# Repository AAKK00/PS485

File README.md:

# PS485
posision sensorとrs485とattinyを用いた角度取得モジュール

Arduinoスケッチ、DynamixelSlaveライブラリ、配線・書き込み手順は [arduino/README.md](arduino/README.md) を参照。

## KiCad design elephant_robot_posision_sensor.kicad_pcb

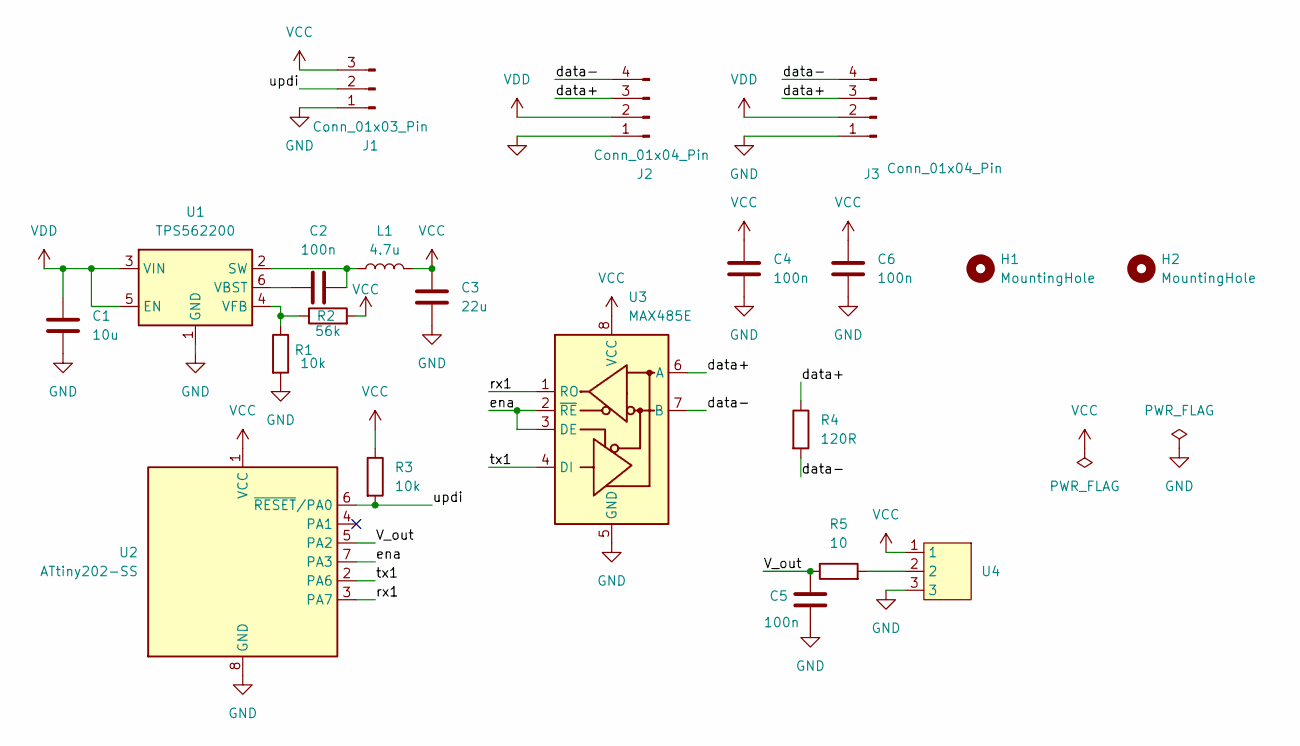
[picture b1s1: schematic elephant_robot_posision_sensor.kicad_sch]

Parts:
C1: 10u; C_0603_1608Metric
C2, C4, C5, C6: 100n; C_0603_1608Metric
C3: 22u; C_0603_1608Metric
H1, H2: MountingHole; MountingHole_2.2mm_M2
J1: Conn_01x03_Pin; PinHeader_1x03_P1.00mm_Vertical
J2, J3: Conn_01x04_Pin; JST_SH_SM04B-SRSS-TB_1x04-1MP_P1.00mm_Horizontal
L1: 4.7u; L_Cenker_CKCS201610
R1: 10k; R_0603_1608Metric
R2: 56k; R_0603_1608Metric
R3: 10k; C_0603_1608Metric
R4: 120R; C_0603_1608Metric
R5: 10; C_0603_1608Metric
U1: TPS562200; SOT-23-6
U2: ATtiny202-SS; SOIC-8_3.9x4.9mm_P1.27mm
U3: MAX485E; SOIC-8_3.9x4.9mm_P1.27mm
U4: RDC506018A

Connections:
/V_out: C5.1, R5.1, U2.5 (PA2)
/data+: J2.3, J3.3, R4.1, U3.6 (A)
/data-: J2.4, J3.4, R4.2, U3.7 (B)
/ena: U2.7 (PA3), U3.2 (~RE), U3.3 (DE)
/rx1: U2.3 (PA7), U3.1 (RO)
/tx1: U2.2 (PA6), U3.4 (DI)
/updi: J1.2, R3.2, U2.6 (~RESET/PA0)
GND: C1.2, C3.2, C4.2, C5.2, C6.2, J1.1, J2.1, J3.1, R1.2, U1.1 (GND), U2.8 (GND), U3.5 (GND), U4.3
unnamed: R5.2, U4.2
unnamed: C2.1, L1.1, U1.2 (SW)
unnamed: C2.2, U1.6 (VBST)
unnamed: R1.1, R2.1, U1.4 (VFB)
VCC: C3.1, C4.1, C6.1, J1.3, L1.2, R2.2, R3.1, U2.1 (VCC), U3.8 (VCC), U4.1
VDD: C1.1, J2.2, J3.2, U1.3 (VIN), U1.5 (EN)

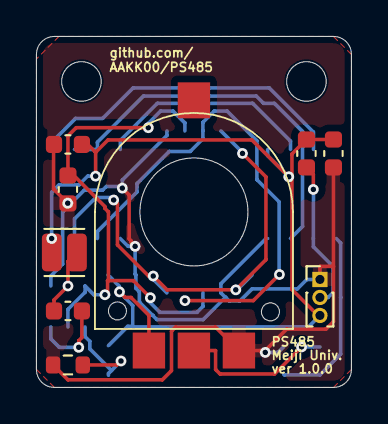
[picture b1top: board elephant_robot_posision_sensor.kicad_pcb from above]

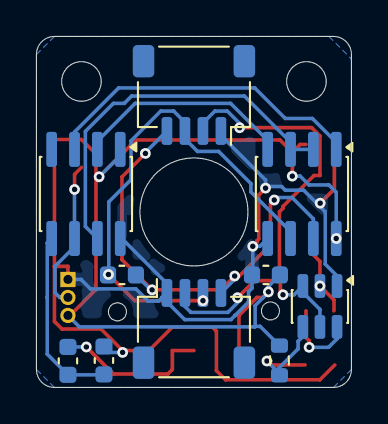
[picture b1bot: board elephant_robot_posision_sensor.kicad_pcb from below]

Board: 2 copper layers, 17.5 x 19.5 mm, 21 parts (10 on the bottom side), 14 nets.

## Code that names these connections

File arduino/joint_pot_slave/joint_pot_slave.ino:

// joint_pot_slave.ino
//
// ATtiny202 Dynamixel Protocol 2.0 slave for the elephant_robot_position_sensor
// board. Reports the potentiometer voltage as "Present Position".
//
// This board wires USART0 to its DEFAULT pins, unlike the older
// JointPotentiometer example (which used the ALT position PA1/PA2):
//   pin 2 (PA6)  tx1   -> MAX485 DI
//   pin 3 (PA7)  rx1   <- MAX485 RO
//   pin 5 (PA2)  V_out <- pot wiper (via 10R + 100n RC)
//   pin 7 (PA3)  ena   -> MAX485 DE+RE (tied)
//   pin 6 (PA0)  UPDI
//
// There is no LED on this board. Control table addr 65 is still writable so
// the master's write path can be exercised; it just lands in RAM.
//
// !!! Set MY_ID per board before burning: one board 100, the other 101 !!!
//
// Tools settings: Chip = ATtiny202, Clock = 20 MHz internal.
// (Library baud is fixed at 57600, computed for 20 MHz -- burn bootloader
//  after changing the clock setting so the fuses match.)

#include <DynamixelSlave.h>

constexpr uint8_t  MY_ID    = 101;       // <-- 100 or 101, per board
constexpr uint16_t MY_MODEL = 0x4B41;
constexpr uint8_t  DIR_PIN  = PIN_PA3;

volatile uint16_t present_position = 0;  // addr 132, RO, 2 bytes
volatile uint8_t  led_state        = 0;  // addr 65,  RW, 1 byte (no physical LED)

DynamixelSlave dxl(MY_ID, MY_MODEL);

// Polled ADC on PA2 (AIN2): ~13.5 us at 20 MHz with DIV16 prescaler.
static void adcInit() {
  ADC0.CTRLC = ADC_PRESC_DIV16_gc | ADC_REFSEL_VDDREF_gc | (1 << ADC_SAMPCAP_bp);
  ADC0.CTRLA = ADC_ENABLE_bm | ADC_RESSEL_10BIT_gc;
  ADC0.MUXPOS = ADC_MUXPOS_AIN2_gc;        // PA2 = V_out
}

static uint16_t adcRead() {
  ADC0.COMMAND = ADC_STCONV_bm;
  while (!(ADC0.INTFLAGS & ADC_RESRDY_bm));
  ADC0.INTFLAGS = ADC_RESRDY_bm;
  return ADC0.RES;
}

void setup() {
  adcInit();

  dxl.addItem(65,  (void*)&led_state,        1, /*readonly*/ false);
  dxl.addItem(132, (void*)&present_position, 2, /*readonly*/ true);

  dxl.setDirectionPin(DIR_PIN);
  dxl.begin(/*alt_pins=*/false);           // this board uses PA6/PA7 (default)
}

void loop() {
  uint16_t raw = adcRead();
  uint8_t sreg = SREG; cli();
  present_position = raw;
  SREG = sreg;

  dxl.process();
}
